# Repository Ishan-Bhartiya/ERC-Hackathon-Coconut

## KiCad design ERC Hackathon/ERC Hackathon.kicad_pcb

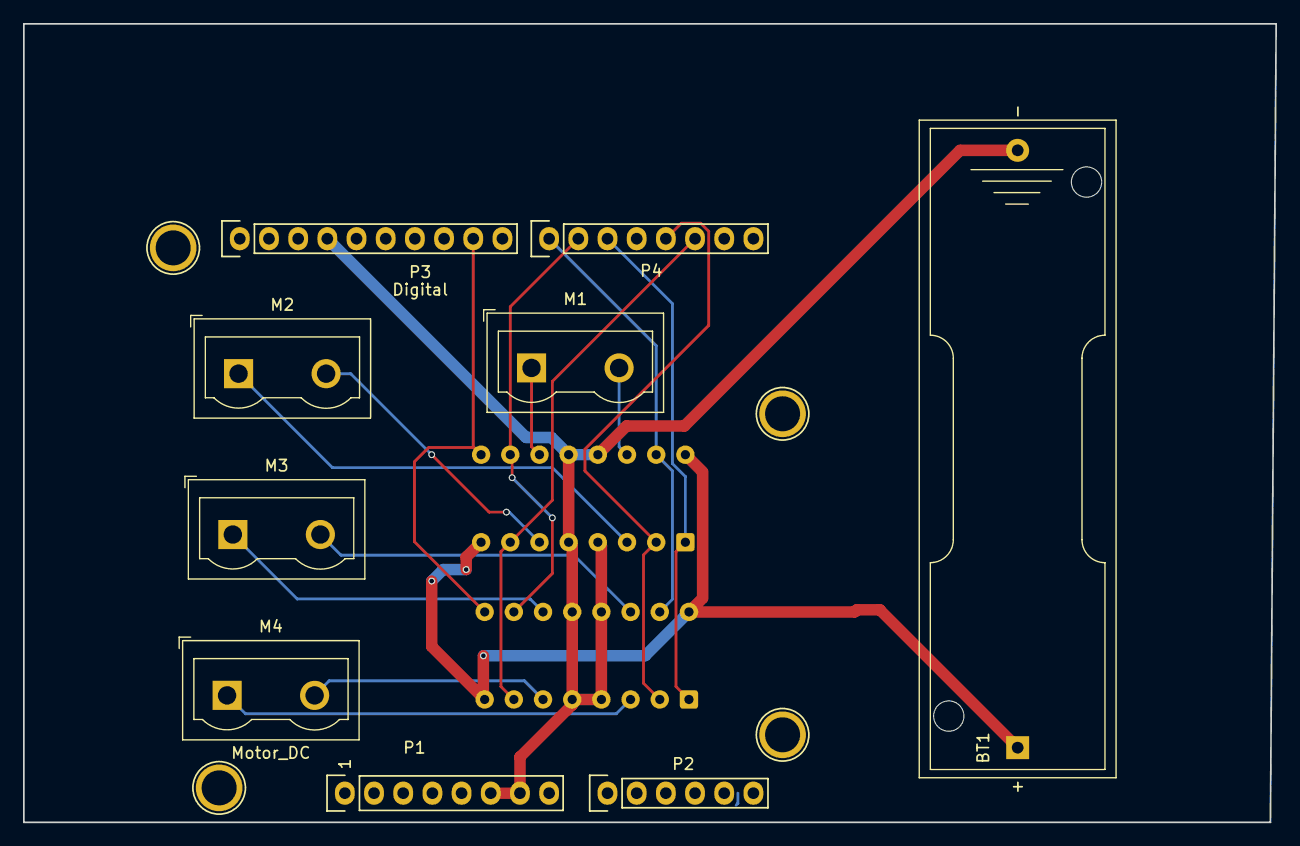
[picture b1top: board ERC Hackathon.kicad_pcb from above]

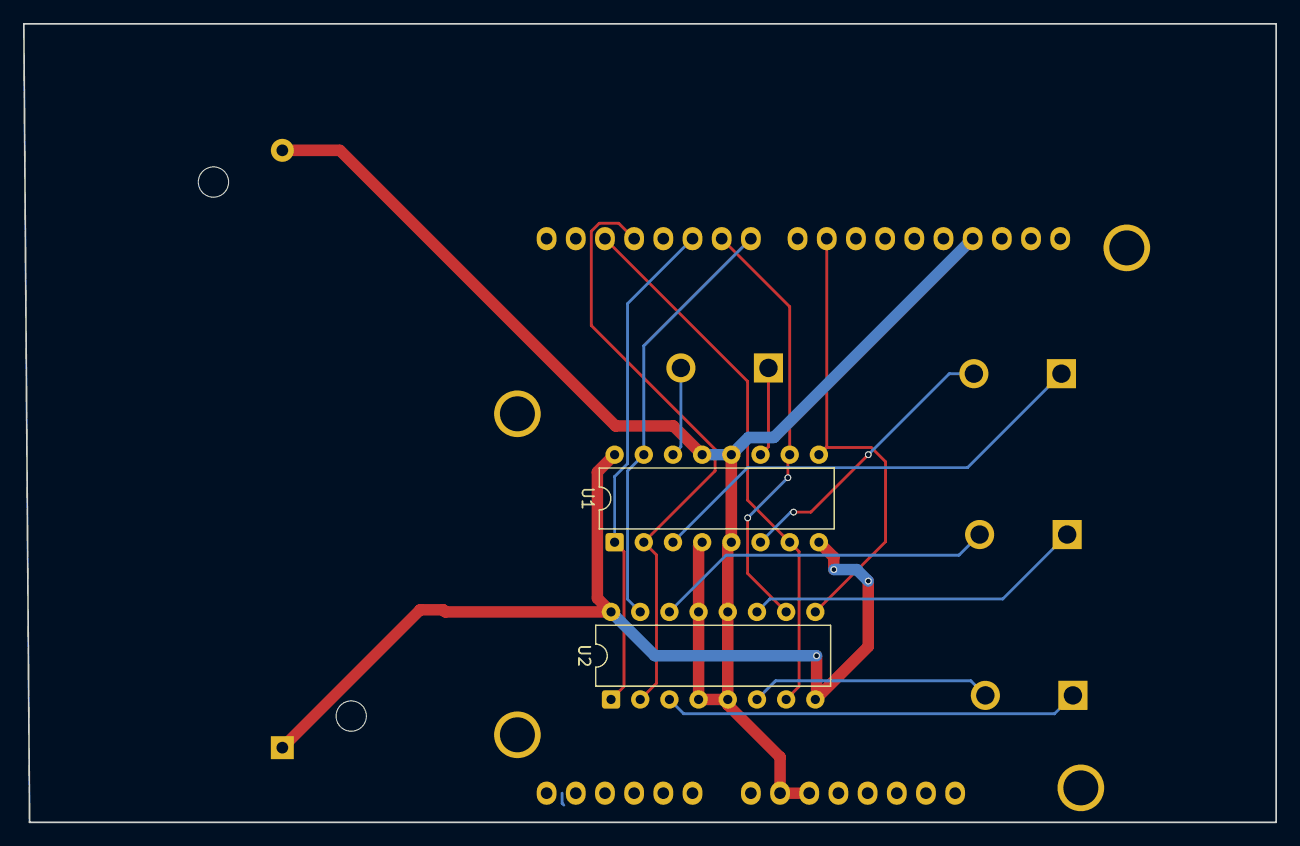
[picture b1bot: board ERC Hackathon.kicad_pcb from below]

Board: 2 copper layers, 109.0 x 69.5 mm, 15 parts (2 on the bottom side), 16 nets.

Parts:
BT1: Battery_Cell; BatteryHolder_Keystone_2460_1xAA
M1, M2, M3, M4: Motor_DC; TerminalBlock_Wuerth_691311400102_P7.62mm
P1: Power; Socket_Strip_Arduino_1x08
P2: Analog; Socket_Strip_Arduino_1x06
P3: Digital; Socket_Strip_Arduino_1x10
P4: Digital; Socket_Strip_Arduino_1x08
P5, P6, P7, P8: CONN_01X01; Arduino_1pin
U1, U2: L293D; DIP-16_W7.62mm

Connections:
+9V: BT1.1 (+), U1.8 (VCC2), U1.16 (VCC1), U2.8 (VCC2), U2.16 (VCC1)
/2: P4.6, U1.7 (2A), U2.7 (2A)
/3(**): P4.5, U1.2 (1A), U2.2 (1A)
/5(**): P4.3, U1.1 (EN1,2), U2.1 (EN1,2)
/6(**): P4.2, U1.10 (3A), U2.10 (3A)
/7: P4.1, U1.15 (4A), U2.15 (4A)
/9(**): P3.9, U1.9 (EN3,4), U2.9 (EN3,4)
/Out-1: M2.1 (+), U1.3 (1Y)
/Out-1': M4.1 (+), U2.3 (1Y)
/Out-2: M2.2 (-), U1.6 (2Y)
/Out-2': M4.2 (-), U2.6 (2Y)
/Out-3: M1.1 (+), U1.11 (3Y)
/Out-3': M3.1 (+), U2.11 (3Y)
/Out-4: M1.2 (-), U1.14 (4Y)
/Out-4': M3.2 (-), U2.14 (4Y)
GND: BT1.2 (-), P1.6, P1.7, P3.4, U1.4 (GND), U1.5 (GND), U1.12 (GND), U1.13 (GND), U2.4 (GND), U2.5 (GND), U2.12 (GND), U2.13 (GND)
